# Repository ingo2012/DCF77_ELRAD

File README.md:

# DCF77_ELRAD
DCF77 RX nach Elrad 04_88

DH1AAD ,Ingo Gerlach , 06.12.2021

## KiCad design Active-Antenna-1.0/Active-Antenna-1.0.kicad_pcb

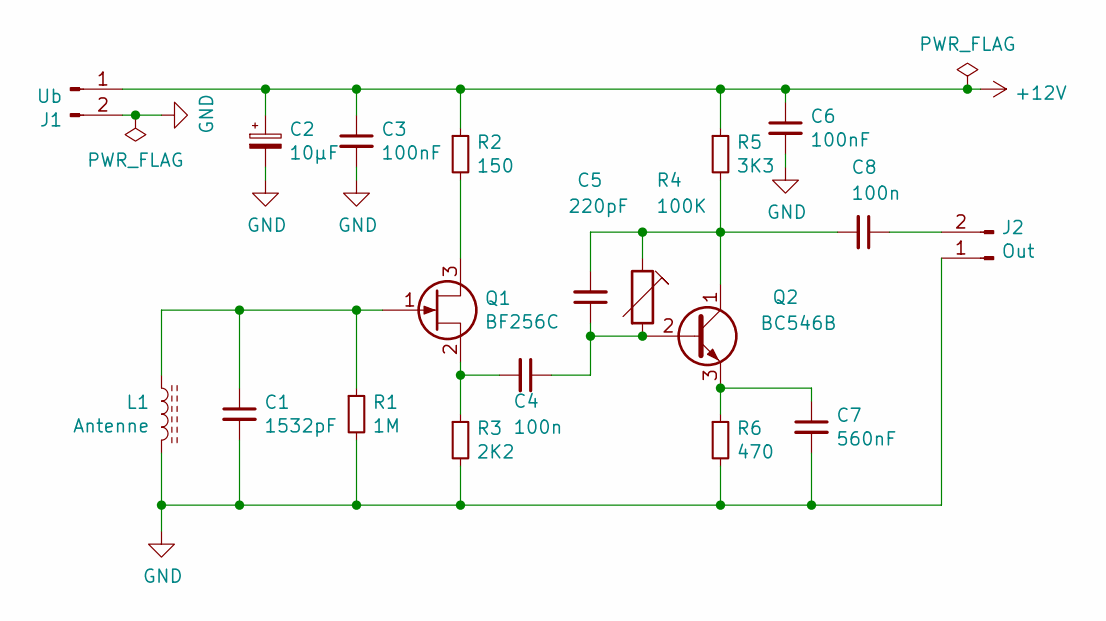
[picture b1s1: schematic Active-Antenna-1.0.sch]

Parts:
C1: 1532pF; C_Rect_L4.6mm_W3.0mm_P2.50mm_MKS02_FKP02
C2: 10µF; CP_Radial_D5.0mm_P2.50mm
C3, C6: 100nF; C_Rect_L4.6mm_W3.0mm_P2.50mm_MKS02_FKP02
C4, C8: 100n; C_Rect_L4.6mm_W3.0mm_P2.50mm_MKS02_FKP02
C5: 220pF; C_Rect_L4.6mm_W3.0mm_P2.50mm_MKS02_FKP02
C7: 560nF; C_Rect_L4.6mm_W3.0mm_P2.50mm_MKS02_FKP02
J1: Ub; PinHeader_1x02_P2.54mm_Vertical
J2: Out; PinHeader_1x02_P2.54mm_Vertical
L1: Antenne; PinHeader_1x02_P2.54mm_Vertical
Q1: BF256C; TO-92_Inline
Q2: BC546B; TO-92_Inline
R1: 1M; R_Axial_DIN0309_L9.0mm_D3.2mm_P12.70mm_Horizontal
R2: 150; R_Axial_DIN0309_L9.0mm_D3.2mm_P12.70mm_Horizontal
R3: 2K2; R_Axial_DIN0309_L9.0mm_D3.2mm_P12.70mm_Horizontal
R4: 100K; Potentiometer_Bourns_3339P_Vertical_HandSoldering
R5: 3K3; R_Axial_DIN0309_L9.0mm_D3.2mm_P12.70mm_Horizontal
R6: 470; R_Axial_DIN0309_L9.0mm_D3.2mm_P12.70mm_Horizontal

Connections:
+12V: C2.1, C3.1, C6.1, J1.1, R2.1, R5.1
GND: C1.2, C2.2, C3.2, C6.2, C7.2, J1.2, J2.1, L1.1, R1.2, R3.2, R6.2
unnamed: C1.1, L1.2, Q1.1 (G), R1.1
unnamed: C4.1, C5.1, Q2.2 (B), R4.2
unnamed: C4.2, Q1.2 (S), R3.1
unnamed: C5.2, C8.2, Q2.1 (C), R4.1, R5.2
unnamed: C7.1, Q2.3 (E), R6.1
unnamed: C8.1, J2.2
unnamed: Q1.3 (D), R2.2

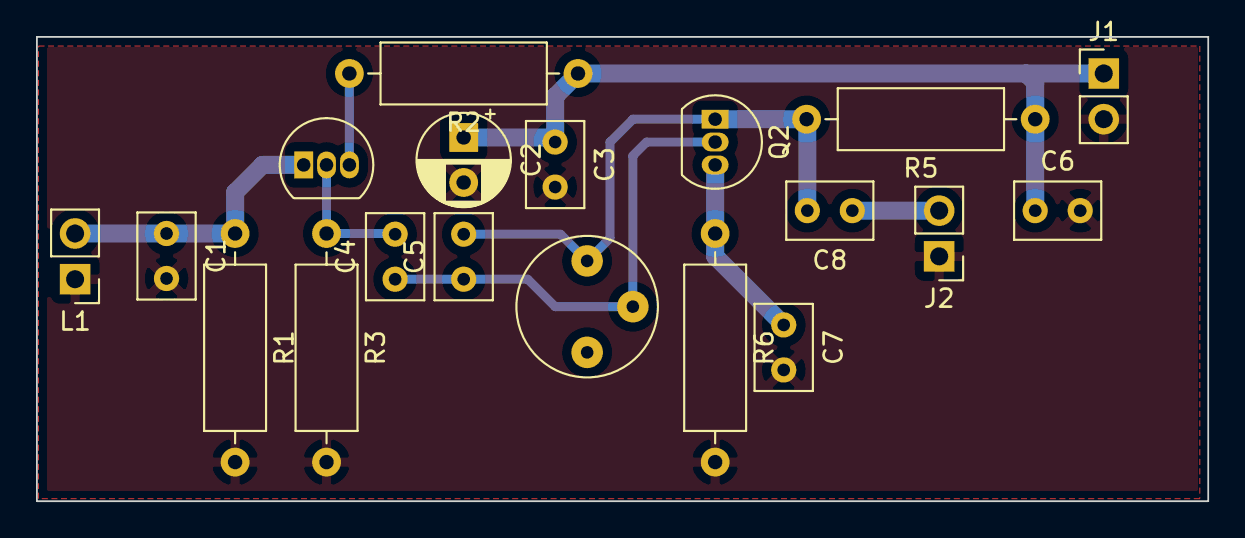
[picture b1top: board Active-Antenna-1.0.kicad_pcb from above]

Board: 2 copper layers, 65.1 x 25.8 mm, 19 parts (0 on the bottom side), 9 nets.

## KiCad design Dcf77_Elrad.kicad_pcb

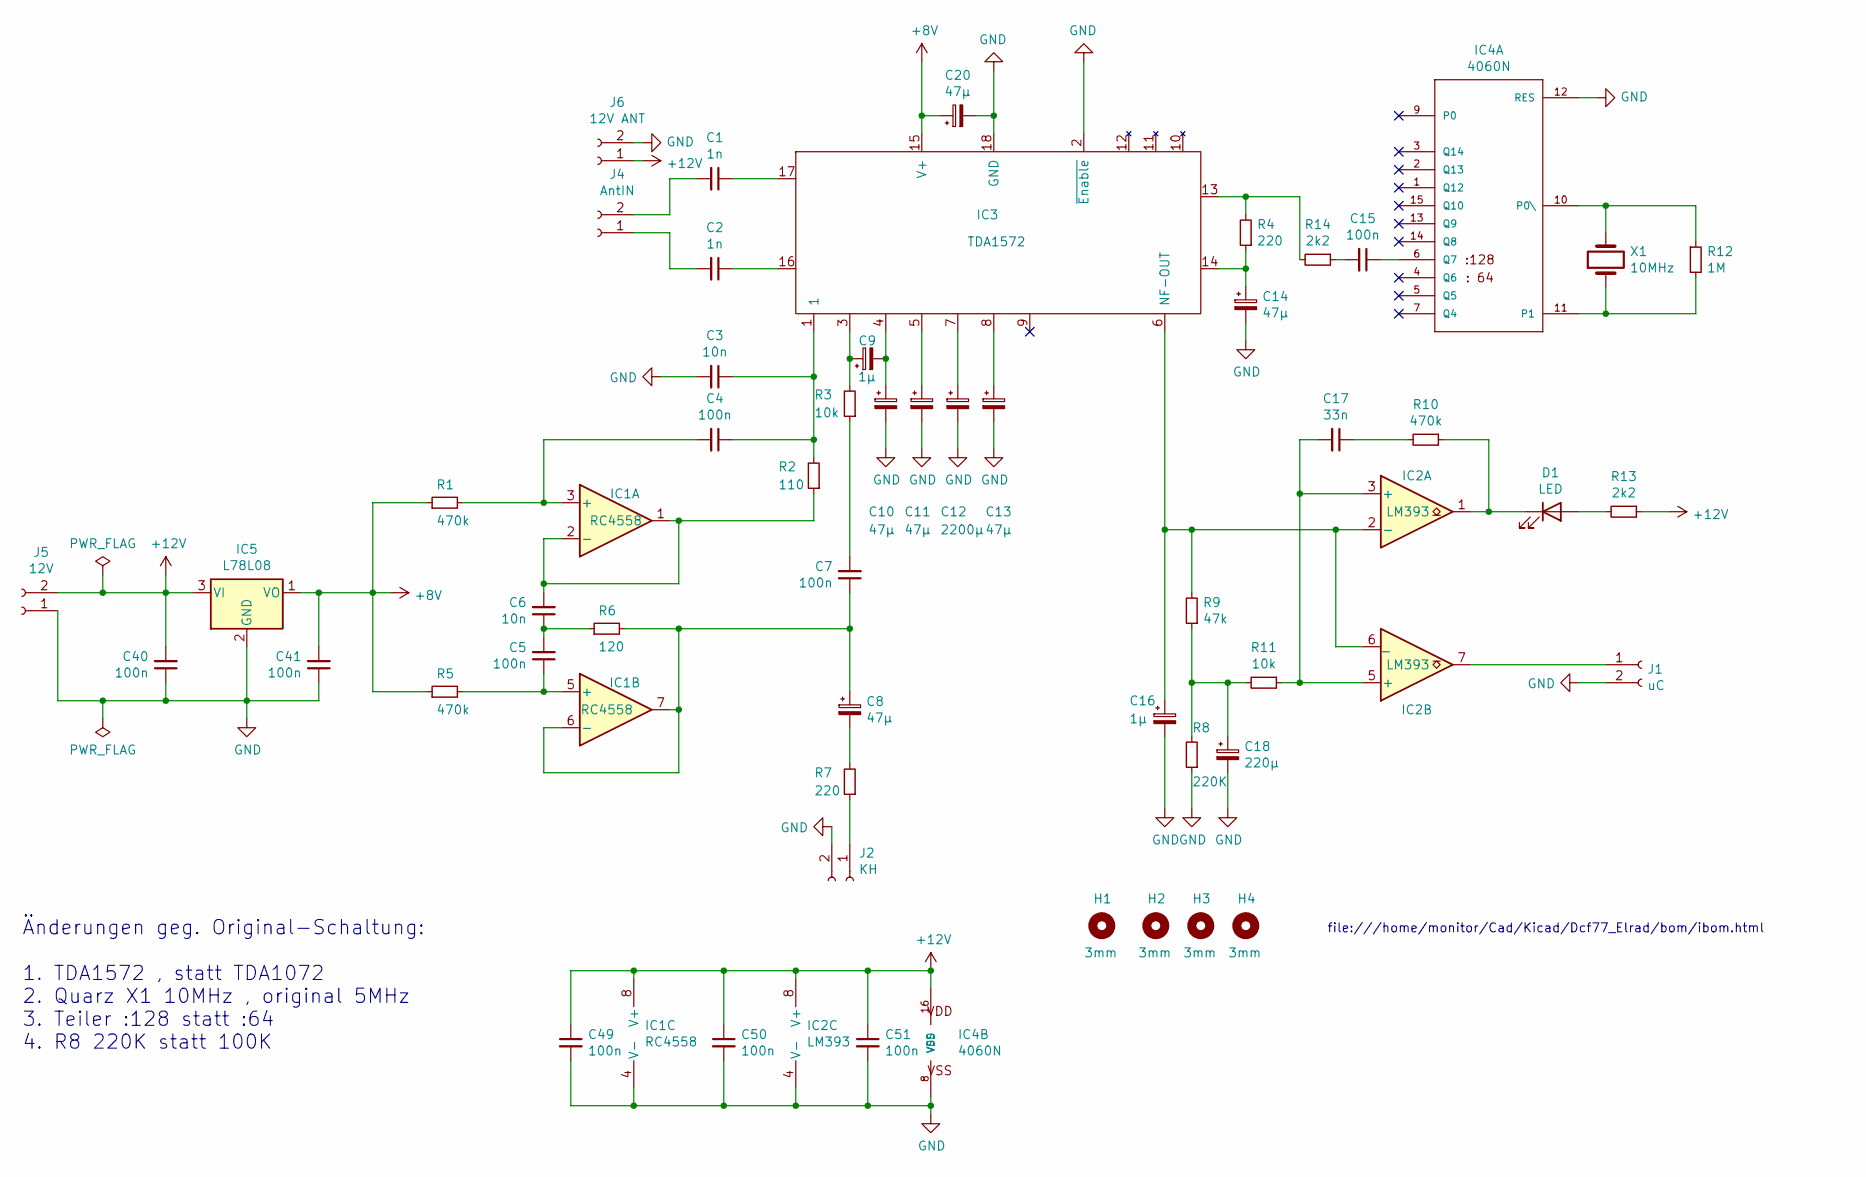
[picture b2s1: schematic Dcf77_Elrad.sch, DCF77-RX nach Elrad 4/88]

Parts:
C1, C2: 1n; C_Rect_L4.6mm_W3.0mm_P2.50mm_MKS02_FKP02
C3, C6: 10n; C_Rect_L4.6mm_W3.0mm_P2.50mm_MKS02_FKP02
C4, C5, C7, C15, C40, C41, C49, C50, C51: 100n; C_Rect_L4.6mm_W3.0mm_P2.50mm_MKS02_FKP02
C8, C10, C11, C13, C14, C20: 47µ; CP_Radial_D6.3mm_P2.50mm
C9, C16: 1µ; CP_Radial_D5.0mm_P2.50mm
C12: 2200µ; CP_Radial_D16.0mm_P7.50mm
C17: 33n; C_Rect_L4.6mm_W3.0mm_P2.50mm_MKS02_FKP02
C18: 220µ; CP_Radial_D10.0mm_P5.00mm
D1: LED; LED_D5.0mm
H1, H2, H3, H4: 3mm; MountingHole_3.2mm_M3
IC1: RC4558; DIP-8_W7.62mm_LongPads
IC2: LM393; DIP-8_W7.62mm_LongPads
IC3: TDA1572; DIP-18_W7.62mm_LongPads
IC4: 4060N; DIP-16_W7.62mm_LongPads
IC5: L78L08; TO-92_Inline
J1: uC; PinHeader_2x01_P2.54mm_Vertical
J2: KH; PinHeader_2x01_P2.54mm_Vertical
J4: AntIN; PinHeader_2x01_P2.54mm_Vertical
J5: 12V; PinHeader_2x01_P2.54mm_Vertical
J6: 12V ANT; PinHeader_2x01_P2.54mm_Vertical
R1, R5, R10: 470k; R_Axial_DIN0207_L6.3mm_D2.5mm_P10.16mm_Horizontal
R2: 110; R_Axial_DIN0207_L6.3mm_D2.5mm_P10.16mm_Horizontal
R3, R11: 10k; R_Axial_DIN0207_L6.3mm_D2.5mm_P10.16mm_Horizontal
R4, R7: 220; R_Axial_DIN0207_L6.3mm_D2.5mm_P10.16mm_Horizontal
R6: 120; R_Axial_DIN0207_L6.3mm_D2.5mm_P10.16mm_Horizontal
R8: 220K; R_Axial_DIN0207_L6.3mm_D2.5mm_P10.16mm_Horizontal
R9: 47k; R_Axial_DIN0207_L6.3mm_D2.5mm_P10.16mm_Horizontal
R12: 1M; R_Axial_DIN0207_L6.3mm_D2.5mm_P10.16mm_Horizontal
R13, R14: 2k2; R_Axial_DIN0207_L6.3mm_D2.5mm_P10.16mm_Horizontal
X1: 10MHz; Crystal_HC49-4H_Vertical

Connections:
+8V: C20.1, C41.2, IC3.15 (V+), IC5.1 (VO), R1.1, R5.1
+12V: C40.2, C49.1, C50.1, C51.1, IC1.8 (V+), IC2.8 (V+), IC4.16 (VDD), IC5.3 (VI), J5.2, J6.1, R13.1
GND: C3.2, C10.2, C11.2, C12.2, C13.2, C14.2, C16.2, C18.2, C20.2, C40.1, C41.1, C49.2, C50.2, C51.2, IC1.4 (V-), IC2.4 (V-), IC3.2 (~Enable), IC3.18 (GND), IC4.8 (VSS), IC4.12 (RES), IC5.2 (GND), J1.2, J2.2, J5.1, J6.2, R8.1
unnamed: C1.1, IC3.17
unnamed: C1.2, J4.2
unnamed: C2.1, IC3.16
unnamed: C2.2, J4.1
unnamed: C3.1, C4.1, IC3.1, R2.2
unnamed: C4.2, IC1.3 (+), R1.2
unnamed: C5.1, IC1.5 (+), R5.2
unnamed: C5.2, C6.1, R6.1
unnamed: C6.2, IC1.1, IC1.2 (-), R2.1
unnamed: C7.1, C8.1, IC1.6 (-), IC1.7, R6.2
unnamed: C7.2, R3.1
unnamed: C8.2, R7.2
unnamed: C9.1, IC3.3, R3.2
unnamed: C9.2, C10.1, IC3.4
unnamed: C11.1, IC3.5
unnamed: C12.1, IC3.7
unnamed: C13.1, IC3.8
unnamed: C14.1, IC3.14, R4.1
unnamed: C15.1, IC4.6 (Q7)
unnamed: C15.2, R14.1
unnamed: C16.1, IC2.2 (-), IC2.6 (_), IC3.6 (NF-OUT), R9.2
unnamed: C17.1, R10.2
unnamed: C17.2, IC2.3 (+), IC2.5 (+), R11.1
unnamed: C18.1, R8.2, R9.1, R11.2
unnamed: D1.1 (K), IC2.1, R10.1
unnamed: D1.2 (A), R13.2
unnamed: IC2.7, J1.1
unnamed: IC3.13, R4.2, R14.2
unnamed: IC4.10 (P0\), R12.1, X1.2
unnamed: IC4.11 (P1), R12.2, X1.1
unnamed: J2.1, R7.1

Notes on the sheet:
file:///home/monitor/Cad/Kicad/Dcf77_Elrad/bom/ibom.html
Änderungen geg. Original-Schaltung: 1. TDA1572 , statt TDA1072 2. Quarz X1 10MHz , original 5MHz 3. Teiler :128 statt :64 4. R8 220K statt 100K

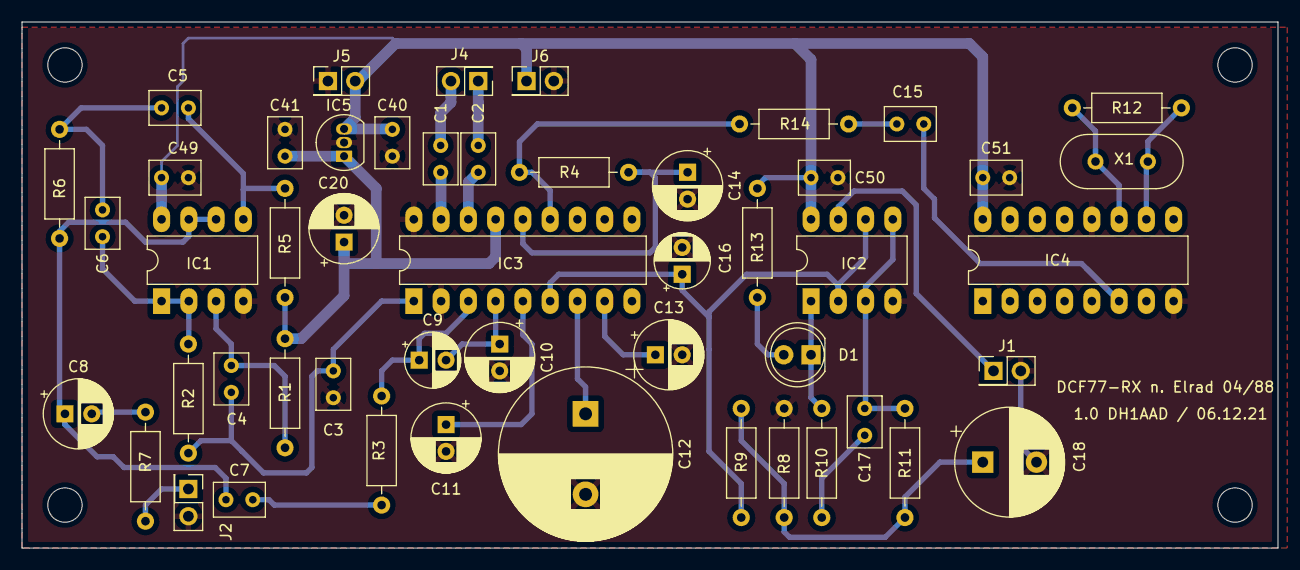
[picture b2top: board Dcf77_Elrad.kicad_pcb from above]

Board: 2 copper layers, 117.0 x 49.0 mm, 54 parts (0 on the bottom side), 34 nets.

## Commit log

2022-01-07 add initial Files
2022-01-07 add Libs
2022-01-07 add ctive-Antenna
2022-01-07 Add Arduino-Board
2022-01-07 Add Gerber files
2022-01-07 Add Software for Nano-V3
2022-01-07 add images
2022-01-07 Add Datasheets
2022-01-07 add Arduino-Board/Arduino.pdf
2022-02-23 add RTC, some Fotos
